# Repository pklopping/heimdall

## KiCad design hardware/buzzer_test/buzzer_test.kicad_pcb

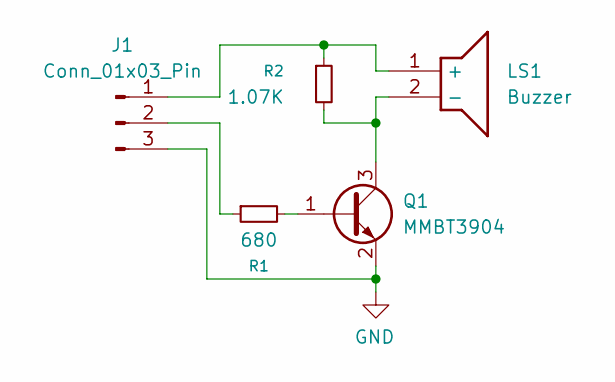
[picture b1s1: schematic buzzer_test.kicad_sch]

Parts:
J1: Conn_01x03_Pin; PinHeader_1x03_P2.54mm_Vertical
LS1: Buzzer; CMT1075SMTTR; Mouser Part Number 490-CMT-1075-SMT-TR
Q1: MMBT3904; SOT-23
R1: 680; R_0805_2012Metric
R2: 1.07K; R_0805_2012Metric

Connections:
GND: J1.3, Q1.2 (E)
unnamed: J1.1, LS1.1 (+), R2.1
unnamed: J1.2, R1.1
unnamed: LS1.2 (-), Q1.3 (C), R2.2
unnamed: Q1.1 (B), R1.2

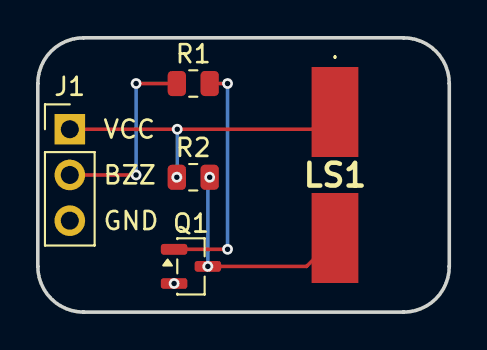
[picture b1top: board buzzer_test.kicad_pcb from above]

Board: 2 copper layers, 22.9 x 15.2 mm, 5 parts (0 on the bottom side), 5 nets.

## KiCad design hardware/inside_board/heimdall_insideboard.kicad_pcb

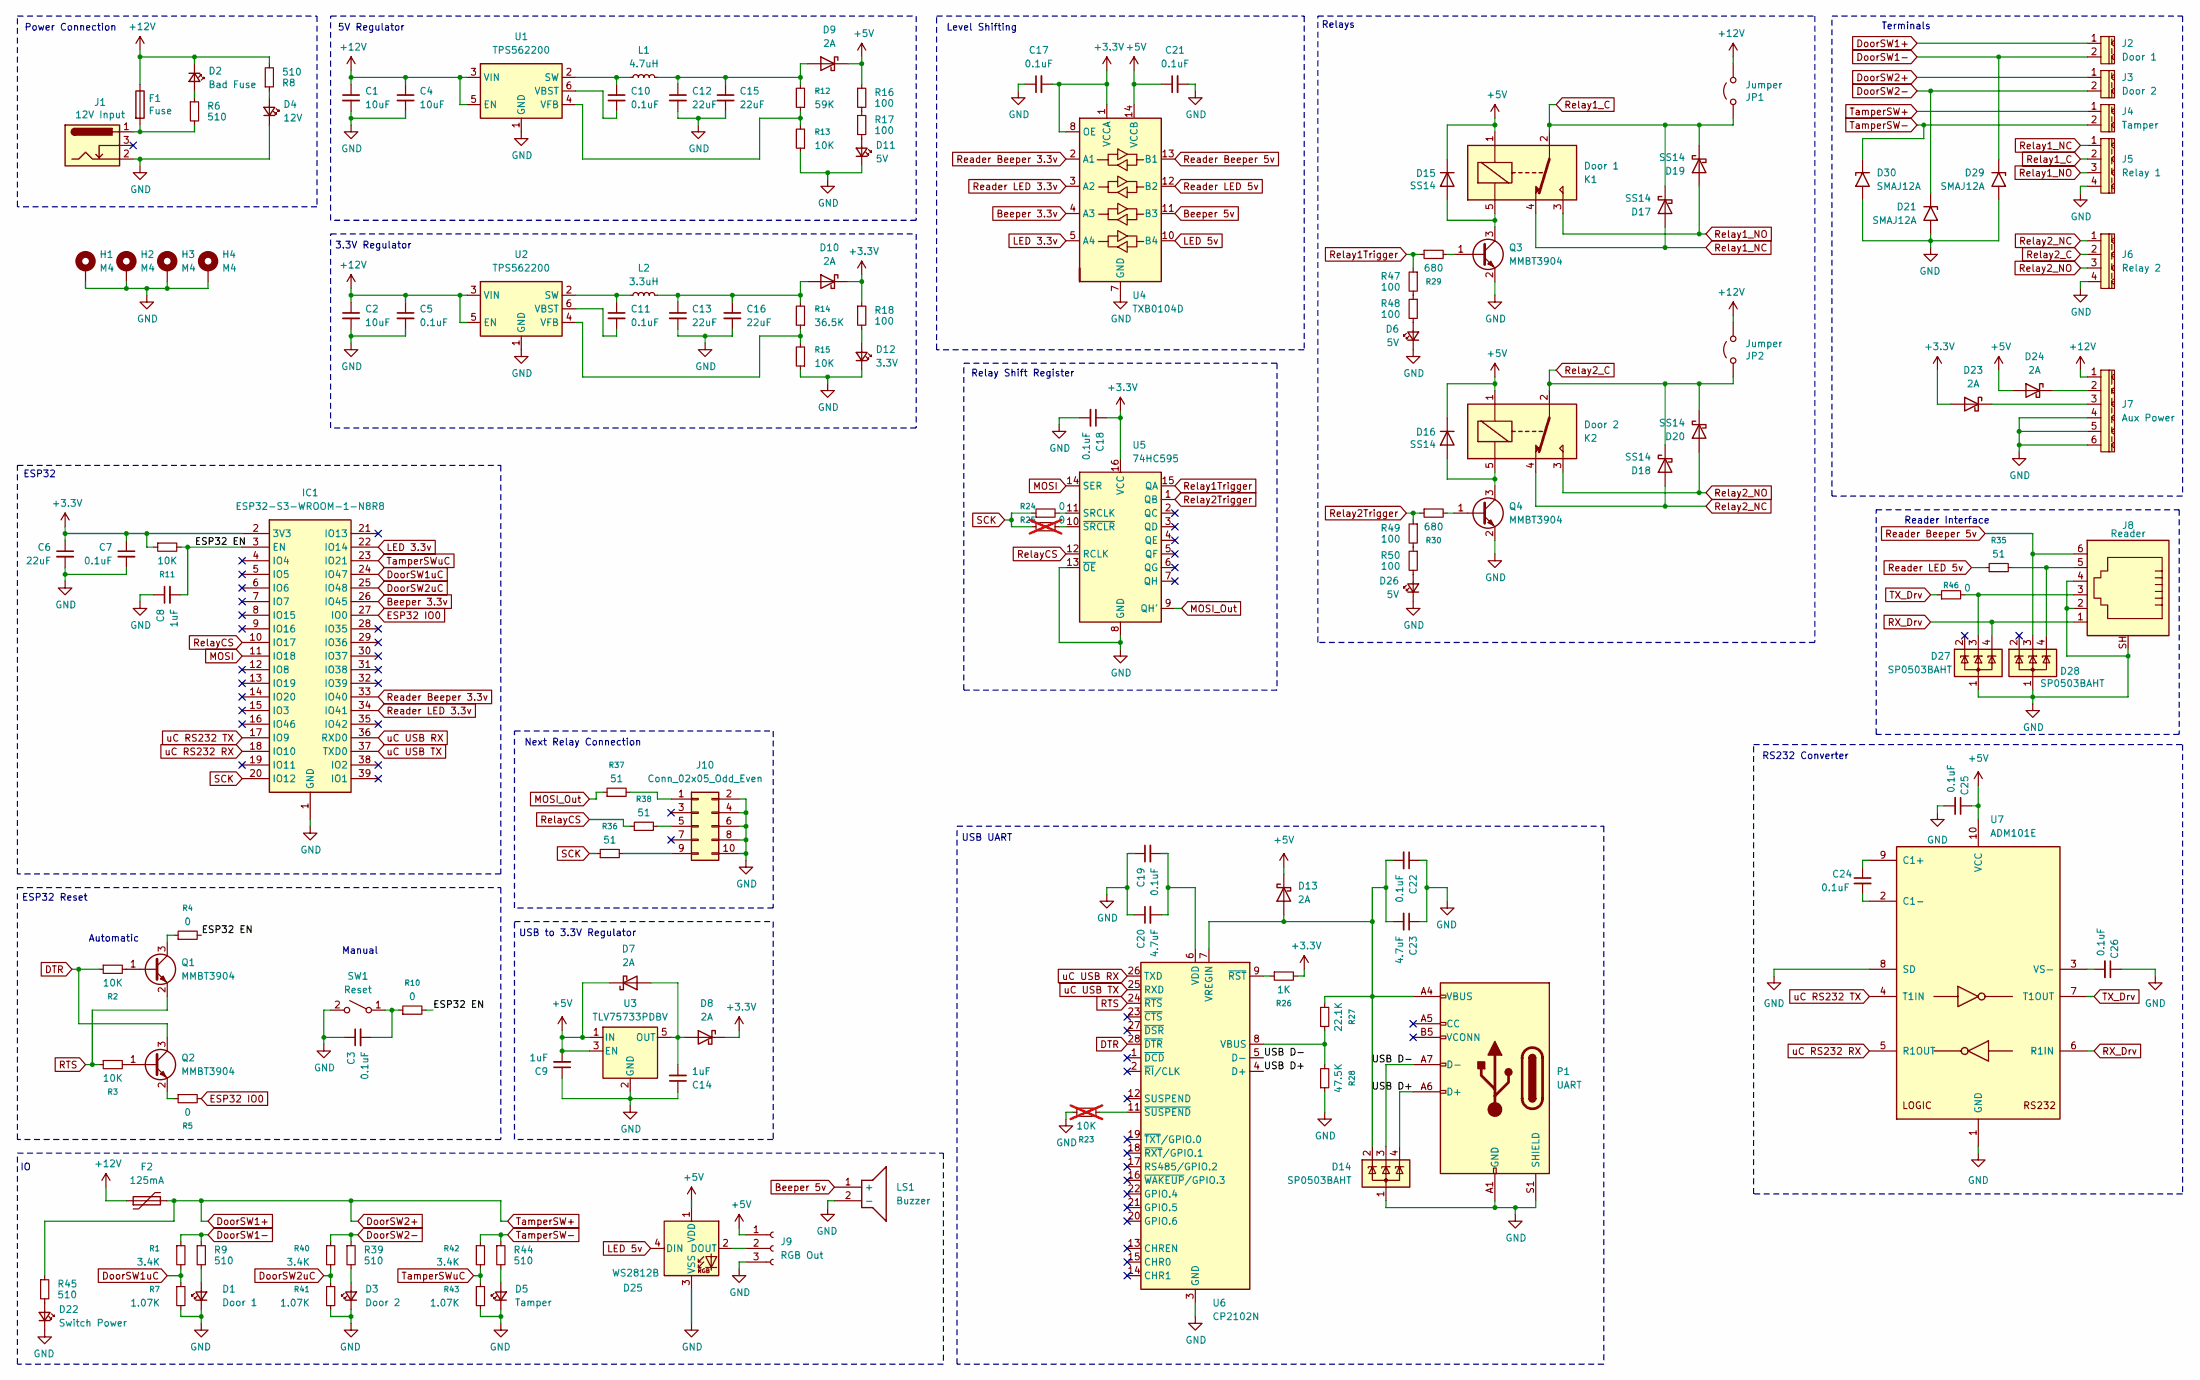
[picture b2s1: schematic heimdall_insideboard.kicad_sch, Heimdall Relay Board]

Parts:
C1, C2, C4: 10uF; C_0805_2012Metric
C3, C5, C7, C10, C11, C17, C18, C19, C21, C22, C24, C25, C26: 0.1uF; C_0805_2012Metric
C6, C12, C13, C15, C16: 22uF; C_0805_2012Metric
C8, C9, C14: 1uF; C_0805_2012Metric
C20, C23: 4.7uF; C_0805_2012Metric
D1: Door 1; LED_0805_2012Metric
D2: Bad Fuse; LED_0805_2012Metric
D3: Door 2; LED_0805_2012Metric
D4: 12V; LED_0805_2012Metric
D5: Tamper; LED_0805_2012Metric
D6, D11, D26: 5V; LED_0805_2012Metric
D7, D8, D9, D10, D13, D23, D24: 2A; D_SMB
D12: 3.3V; LED_0805_2012Metric
D14, D27, D28: SP0503BAHT; SOT-143
D15, D16, D17, D18, D19, D20: SS14; D_SMA
D21, D29, D30: SMAJ12A; D_SMA
D22: Switch Power; LED_0805_2012Metric
D25: WS2812B; LED_WS2812B_PLCC4_5.0x5.0mm_P3.2mm
F1: Fuse; Fuseholder_Clip-5x20mm_Littelfuse_521_Lateral_P17.00x5.00mm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
F2: 125mA; Fuse_1206_3216Metric
H1, H2, H3, H4: M4; MountingHole_4.3mm_M4_Pad_Via
IC1: ESP32-S3-WROOM-1-N8R8; ESP32S3WROOM1N8R8; Mouser Part Number 356-EP32S3WROOM1N8R8
J1: 12V Input; BarrelJack_Wuerth_6941xx301002
J2: Door 1; 1759017
J3: Door 2; 1759017
J4: Tamper; 1759017
J5: Relay 1; 1759033
J6: Relay 2; 1759033
J7: Aux Power; 1759059
J8: Reader; CRJ0241TH
J9: RGB Out; PinHeader_1x03_P2.54mm_Vertical
J10: Conn_02x05_Odd_Even; 75869-101LF
JP1, JP2: Jumper; PinHeader_1x03_P2.54mm_Vertical
K1: Door 1; G6RN17EASICFHADC5; Manufacturer_Part_Number G6RN-17-E-ASI-CF-HA DC5
K2: Door 2; G6RN17EASICFHADC5; Manufacturer_Part_Number G6RN-17-E-ASI-CF-HA DC5
L1: 4.7uH; SRR1260A4R7Y
L2: 3.3uH; SRR1260A4R7Y
LS1: Buzzer; CMT1075SMTTR; Mouser Part Number 490-CMT-1075-SMT-TR
P1: UART; USB4920-00-A
Q1, Q2, Q3, Q4: MMBT3904; SOT-23
R1, R40, R42: 3.4K; R_0805_2012Metric
R2, R3, R11, R13, R15: 10K; R_0805_2012Metric
R4, R5, R10, R24, R46: 0; R_0805_2012Metric
R6, R8, R9, R39, R44, R45: 510; R_0805_2012Metric
R7, R41, R43: 1.07K; R_0805_2012Metric
R12: 59K; R_0805_2012Metric
R14: 36.5K; R_0805_2012Metric
R16, R17, R18, R47, R48, R49, R50: 100; R_0805_2012Metric
R23: 10K; R_0805_2012Metric; not fitted
R25: 0; R_0805_2012Metric; not fitted
R26: 1K; R_0805_2012Metric
R27: 22.1K; R_0805_2012Metric
R28: 47.5K; R_0805_2012Metric
R29, R30: 680; R_0805_2012Metric
R35, R36, R37, R38: 51; R_0805_2012Metric
SW1: Reset; SW_SPST_Omron_B3FS-100xP
U1, U2: TPS562200; SOT-23-6
U3: TLV75733PDBV; SOT-23-5
U4: TXB0104D; SOIC-14_3.9x8.7mm_P1.27mm
U5: 74HC595; SOIC-16W_7.5x10.3mm_P1.27mm
U6: CP2102N; QFN-28-1EP_5x5mm_P0.5mm_EP3.35x3.35mm
U7: ADM101E; MSOP-10_3x3mm_P0.5mm

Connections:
+3.3V: C6.1, C7.1, C17.2, C18.1, D8.1 (K), D10.1 (K), D23.2 (A), IC1.2 (3V3), R11.1, R18.1, R26.2, U4.1 (VCCA), U4.8 (OE), U5.16 (VCC)
+5V: C9.2, C21.1, C25.1, D7.1 (K), D9.1 (K), D13.1 (K), D15.1 (K), D16.1 (K), D24.2 (A), D25.1 (VDD), J9.1, K1.1, K2.1, R16.1, U3.1 (IN), U3.3 (EN), U4.14 (VCCB), U7.10 (VCC)
+12V: C1.1, C2.1, C4.1, C5.1, D2.1 (K), F1.1, F2.1, J7.1, JP1.1 (A), JP2.1 (A), R8.2, U1.3 (VIN), U1.5 (EN), U2.3 (VIN), U2.5 (EN)
/ESP32 EN: C8.2, IC1.3 (EN), R4.2, R10.2, R11.2
/USB D+: D14.4 (K), P1.A6 (D+), U6.4 (D+)
/USB D-: D14.3 (K), P1.A7 (D-), U6.5 (D-)
Beeper 3.3v: IC1.26 (IO45), U4.4 (A3)
Beeper 5v: LS1.1 (+), U4.11 (B3)
DTR: Q2.3 (C), R2.1, U6.28 (~DTR)
DoorSW1+: F2.2, J2.1, J3.1, J4.1, R45.1
DoorSW1-: D29.1 (A1), J2.2, R1.1, R9.1
DoorSW1uC: IC1.24 (IO47), R1.2, R7.1
DoorSW2-: D21.1 (A1), J3.2, R39.1, R40.1
DoorSW2uC: IC1.25 (IO48), R40.2, R41.1
ESP32 IO0: IC1.27 (IO0), R5.2
GND: C1.2, C2.2, C3.1, C4.2, C5.2, C6.2, C7.2, C8.1, C9.1, C12.2, C13.2, C14.1, C15.2, C16.2, C17.1, C18.2, C19.1, C20.1, C21.2, C22.1, C23.1, C25.2, C26.1, D1.1 (K), D3.1 (K), D4.1 (K), D5.1 (K), D6.1 (K), D11.1 (K), D12.1 (K), D14.1 (A), D21.2 (A2), D22.1 (K), D25.3 (VSS), D26.1 (K), D27.1 (A), D28.1 (A), D29.2 (A2), D30.2 (A2), H1.1, H2.1, H3.1, H4.1, IC1.1 (GND), J1.2, J5.4, J6.4, J7.4, J7.5, J7.6, J8.2, J8.4, J8.SH, J9.3, J10.2, J10.4, J10.6, J10.8, J10.10, LS1.2 (-), P1.A1 (GND), P1.A12 (GND), P1.B1 (GND), P1.B12 (GND), P1.S1 (SHIELD), Q3.2 (E), Q4.2 (E), R7.2, R13.1, R15.1, R23.1, R28.1, R41.2, R43.2, SW1.2 (B), U1.1 (GND), U2.1 (GND), U3.2 (GND), U4.7 (GND), U5.8 (GND), U5.13 (~OE), U6.3 (GND), U6.29 (GND), U7.1 (GND), U7.8 (SD)
LED 3.3v: IC1.22 (IO14), U4.5 (A4)
LED 5v: D25.4 (DIN), U4.10 (B4)
MOSI: IC1.11 (IO18), U5.14 (SER)
MOSI_Out: R37.1, U5.9 (QH')
unnamed: D1.2 (A), R9.2
unnamed: D2.2 (A), R6.1
unnamed: D3.2 (A), R39.2
unnamed: D4.2 (A), R8.1
unnamed: D5.2 (A), R44.2
unnamed: D6.2 (A), R48.2
unnamed: C14.2, D7.2 (A), D8.2 (A), U3.5 (OUT)
unnamed: C12.1, C15.1, D9.2 (A), L1.2, R12.2
unnamed: C13.1, C16.1, D10.2 (A), L2.2, R14.2
unnamed: D11.2 (A), R17.2
unnamed: D12.2 (A), R18.2
unnamed: C22.2, C23.2, D13.2 (A), D14.2 (K), P1.A4 (VBUS), P1.A9 (VBUS), P1.B4 (VBUS), P1.B9 (VBUS), R27.2, U6.7 (VREGIN)
unnamed: D15.2 (A), K1.5, Q3.3 (C)
unnamed: D16.2 (A), K2.5, Q4.3 (C)
unnamed: D22.2 (A), R45.2
unnamed: D23.1 (K), J7.3
unnamed: D24.1 (K), J7.2
unnamed: D25.2 (DOUT), J9.2
unnamed: D26.2 (A), R50.2
unnamed: D27.3 (K), J8.3, R46.2
unnamed: D28.4 (K), J8.5, R35.2
unnamed: F1.2, J1.1, R6.2
unnamed: J10.1, R37.2
unnamed: J10.5, R38.2
unnamed: J10.9, R36.2
unnamed: Q1.1 (B), R2.2
unnamed: Q1.3 (C), R4.1
unnamed: Q2.1 (B), R3.2
unnamed: Q2.2 (E), R5.1
unnamed: Q3.1 (B), R29.2
unnamed: Q4.1 (B), R30.2
unnamed: R16.2, R17.1
unnamed: R47.2, R48.1
unnamed: R49.2, R50.1
unnamed: C3.2, R10.1, SW1.1 (A)
unnamed: C10.1, L1.1, U1.2 (SW)
unnamed: C10.2, U1.6 (VBST)
unnamed: R12.1, R13.2, U1.4 (VFB)
unnamed: C11.1, L2.1, U2.2 (SW)
unnamed: C11.2, U2.6 (VBST)
unnamed: R14.1, R15.2, U2.4 (VFB)
unnamed: R24.2, U5.11 (SRCLK)
unnamed: R25.2, U5.10 (~SRCLR)
unnamed: R27.1, R28.2, U6.8 (VBUS)
unnamed: C19.2, C20.2, U6.6 (VDD)
unnamed: R26.1, U6.9 (~RST)
unnamed: R23.2, U6.11 (~SUSPEND)
unnamed: C24.1, U7.9 (C1+)
unnamed: C24.2, U7.2 (C1-)
unnamed: C26.2, U7.3 (VS-)
RTS: Q1.2 (E), R3.1, U6.24 (~RTS)
RX_Drv: D27.4 (K), J8.1, U7.6 (R1IN)
Reader Beeper 3.3v: IC1.33 (IO40), U4.2 (A1)
Reader Beeper 5v: D28.3 (K), J8.6, U4.13 (B1)
Reader LED 3.3v: IC1.34 (IO41), U4.3 (A2)
Reader LED 5v: R35.1, U4.12 (B2)
Relay1Trigger: R29.1, R47.1, U5.15 (QA)
Relay1_C: D17.1 (K), D19.1 (K), J5.2, JP1.2 (B), K1.2
Relay1_NC: D17.2 (A), J5.1, K1.4
Relay1_NO: D19.2 (A), J5.3, K1.3
Relay2Trigger: R30.1, R49.1, U5.1 (QB)
Relay2_C: D18.1 (K), D20.1 (K), J6.2, JP2.2 (B), K2.2
Relay2_NC: D18.2 (A), J6.1, K2.4
Relay2_NO: D20.2 (A), J6.3, K2.3
RelayCS: IC1.10 (IO17), R38.1, U5.12 (RCLK)
SCK: IC1.20 (IO12), R24.1, R25.1, R36.1
TX_Drv: R46.1, U7.7 (T1OUT)
TamperSW-: D30.1 (A1), J4.2, R42.1, R44.1
TamperSWuC: IC1.23 (IO21), R42.2, R43.1
uC RS232 RX: IC1.18 (IO10), U7.5 (R1OUT)
uC RS232 TX: IC1.17 (IO9), U7.4 (T1IN)
uC USB RX: IC1.36 (RXD0), U6.26 (TXD)
uC USB TX: IC1.37 (TXD0), U6.25 (RXD)

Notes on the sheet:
Power Connection
Relay Shift Register
Automatic
RS232 Converter
ESP32 Reset
USB to 3.3V Regulator
Terminals
Next Relay Connection
Manual
3.3V Regulator
5V Regulator
Reader Interface
Relays
Level Shifting
USB UART
ESP32

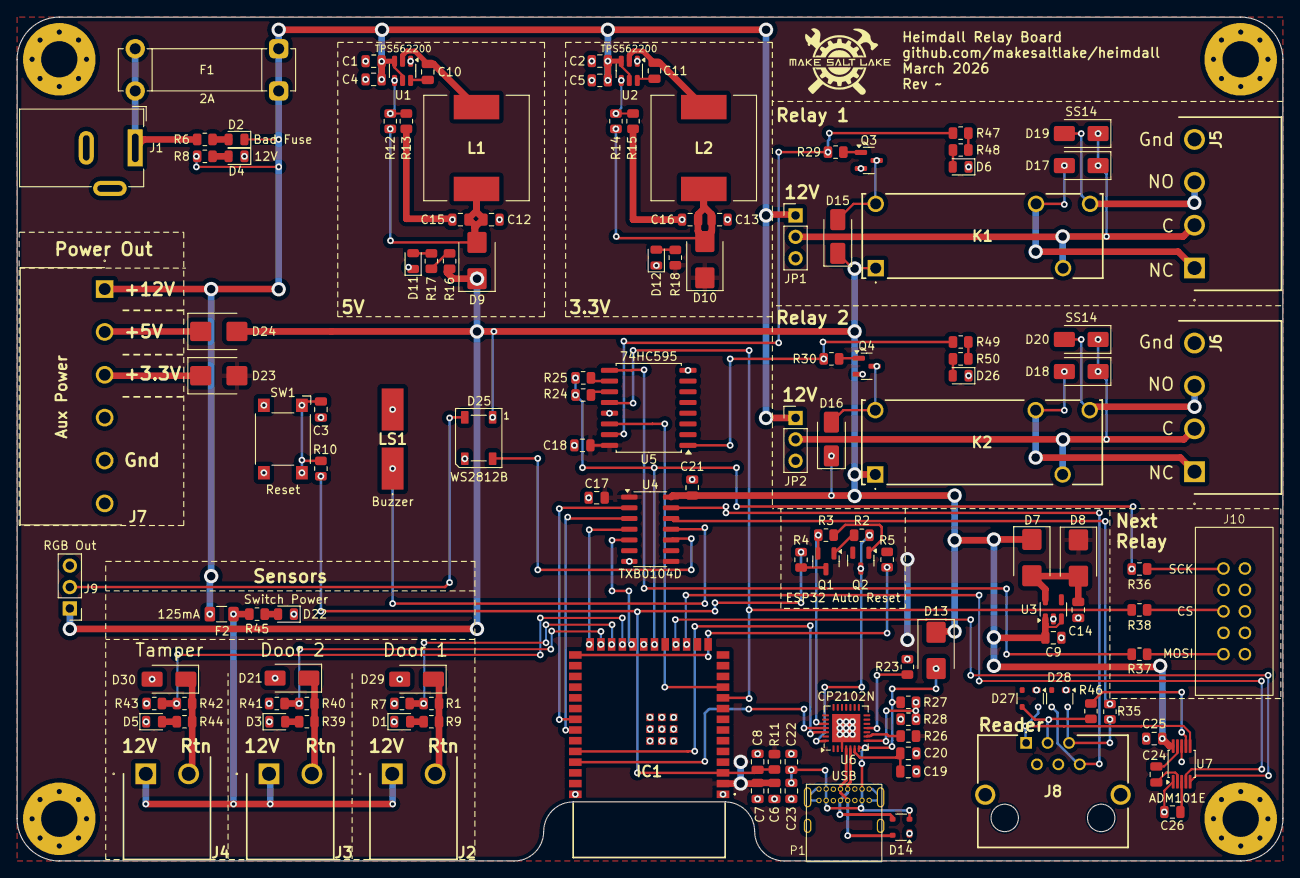
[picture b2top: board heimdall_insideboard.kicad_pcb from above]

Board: 2 copper layers, 150.0 x 100.0 mm, 135 parts (0 on the bottom side), 93 nets.

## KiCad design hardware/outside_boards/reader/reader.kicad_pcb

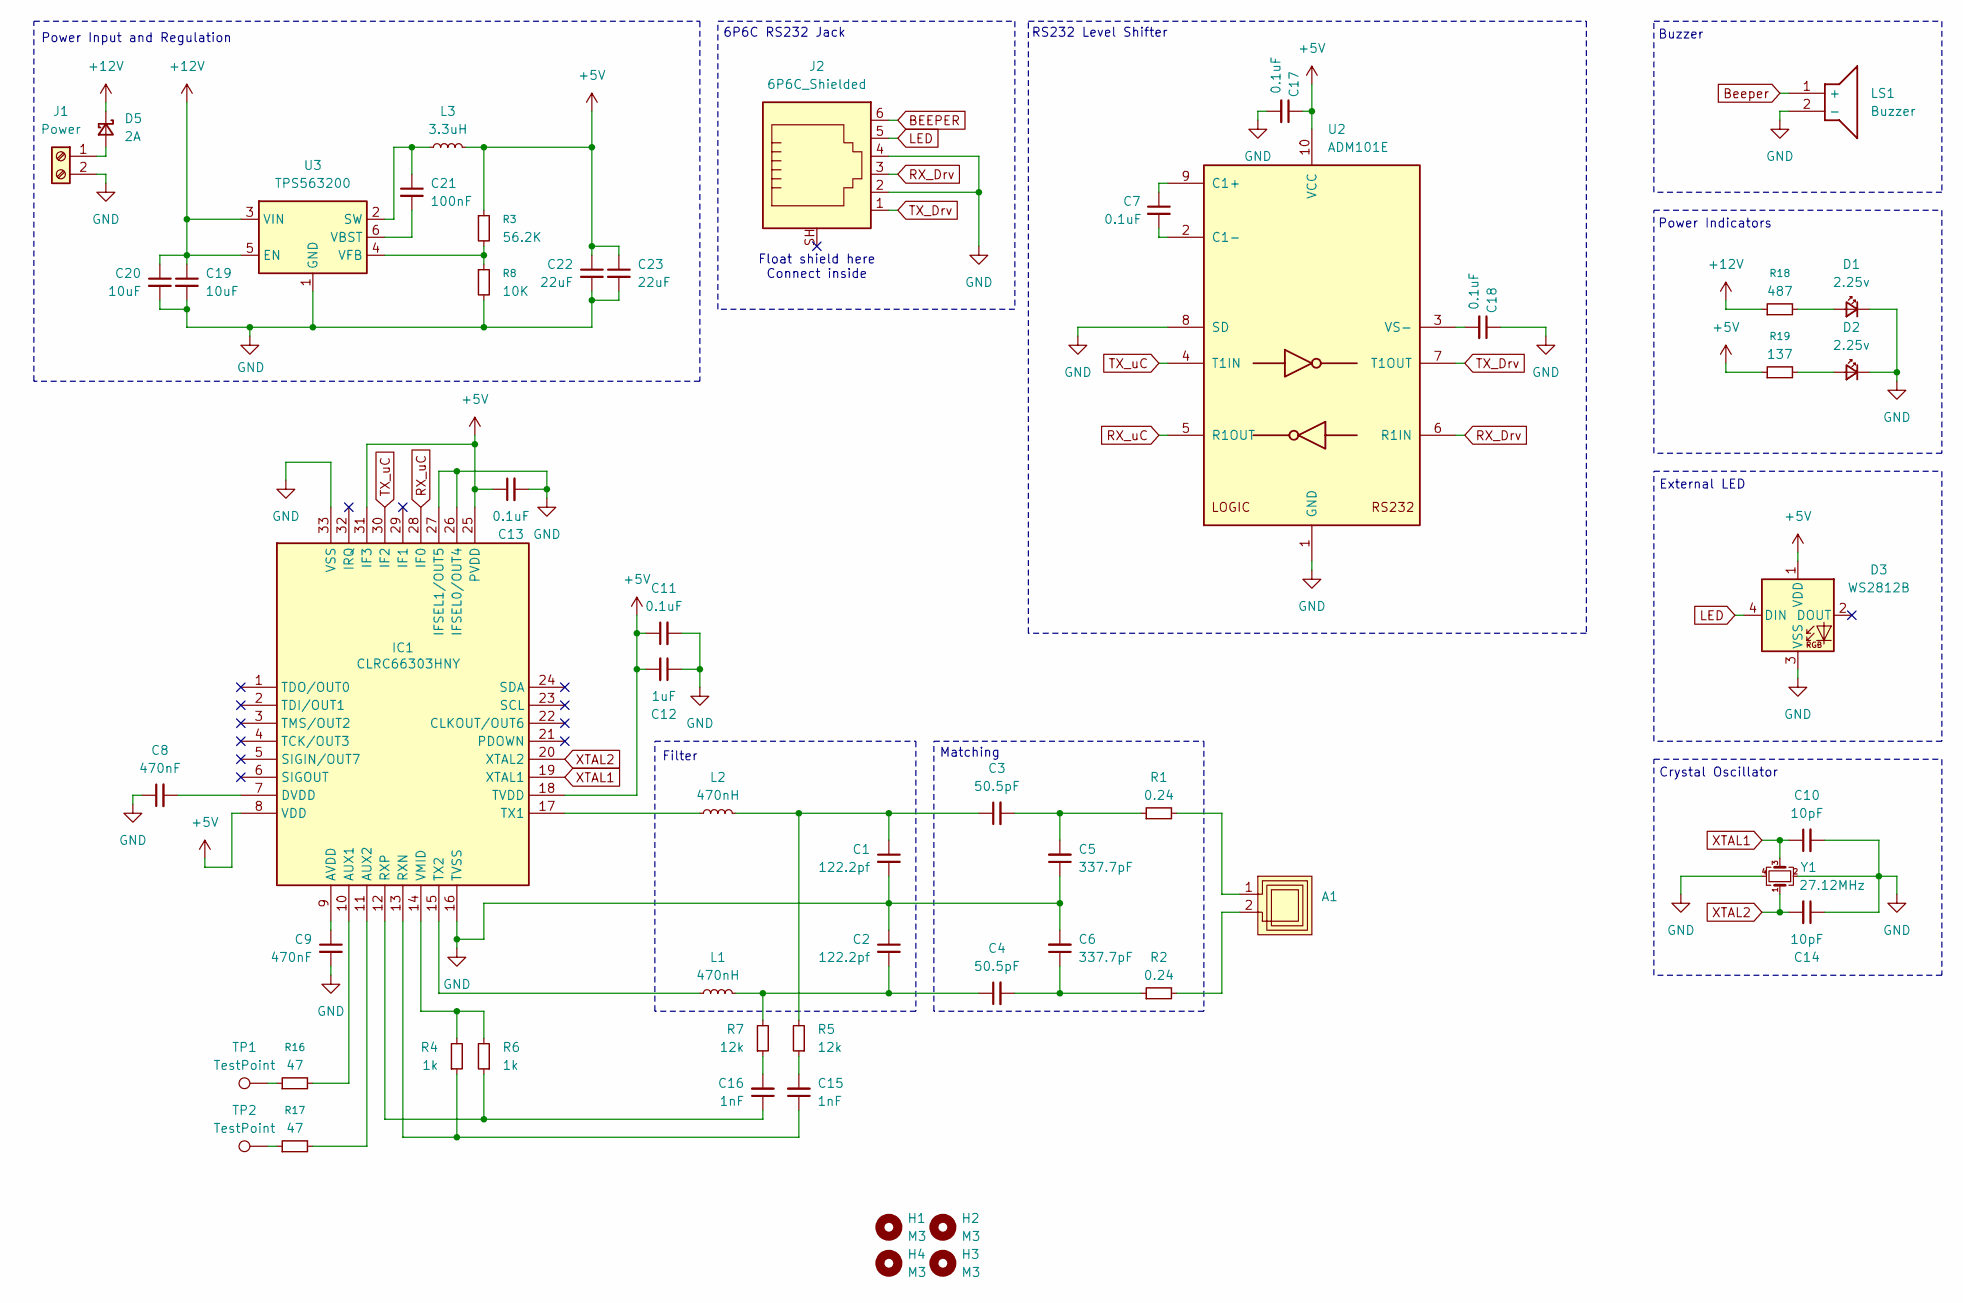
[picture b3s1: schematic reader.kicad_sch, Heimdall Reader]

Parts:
A1: Anetnna_50x50
C1, C2: 122.2pf; C_0805_2012Metric
C3, C4: 50.5pF; C_0805_2012Metric
C5, C6: 337.7pF; C_0805_2012Metric
C7, C11, C13, C17, C18: 0.1uF; C_0805_2012Metric
C8, C9: 470nF; C_0805_2012Metric
C10, C14: 10pF; C_0805_2012Metric
C12: 1uF; C_0805_2012Metric
C15, C16: 1nF; C_0805_2012Metric
C19, C20: 10uF; C_0805_2012Metric
C21: 100nF; C_0805_2012Metric
C22, C23: 22uF; C_0805_2012Metric
D1, D2: 2.25v; LED_0805_2012Metric
D3: WS2812B; LED_WS2812B_PLCC4_5.0x5.0mm_P3.2mm
D5: 2A; D_1206_3216Metric
H1, H2, H3, H4: M3; MountingHole_3.2mm_M3
IC1: CLRC66303HNY; QFN50P500X500X100-33N; Mouser Part Number 771-CLRC66303HNY
J1: Power; 1991095
J2: 6P6C_Shielded; CRJ0241TH
L1, L2: 470nH; L_0805_2012Metric
L3: 3.3uH; L_TDK_VLS6045EX_VLS6045AF
LS1: Buzzer; CMT1075SMTTR; Mouser Part Number 490-CMT-1075-SMT-TR
R1, R2: 0.24; R_0805_2012Metric
R3: 56.2K; R_0805_2012Metric
R4, R6: 1k; R_0805_2012Metric
R5, R7: 12k; R_0805_2012Metric
R8: 10K; R_0805_2012Metric
R16, R17: 47; R_0805_2012Metric
R18: 487; R_0805_2012Metric
R19: 137; R_0805_2012Metric
TP1, TP2: TestPoint; TestPoint_Pad_D1.5mm
U2: ADM101E; MSOP-10_3x3mm_P0.5mm
U3: TPS563200; SOT-23-6
Y1: 27.12MHz; Crystal_SMD_3225-4Pin_3.2x2.5mm

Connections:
+5V: C11.1, C12.2, C13.1, C17.1, C22.1, C23.1, D3.1 (VDD), IC1.8 (VDD), IC1.18 (TVDD), IC1.25 (PVDD), IC1.31 (IF3), L3.2, R3.1, R19.1, U2.10 (VCC)
+12V: C19.1, C20.1, D5.1 (K), R18.1, U3.3 (VIN), U3.5 (EN)
BEEPER: J2.6
Beeper: LS1.1 (+)
GND: C1.2, C2.1, C5.1, C6.2, C8.1, C9.2, C10.2, C11.2, C12.1, C13.2, C14.1, C17.2, C18.1, C19.2, C20.2, C22.2, C23.2, D1.1 (K), D2.1 (K), D3.3 (VSS), IC1.16 (TVSS), IC1.26 (IFSEL0/OUT4), IC1.27 (IFSEL1/OUT5), IC1.33 (VSS), J1.2, J2.2, J2.4, LS1.2 (-), R8.2, U2.1 (GND), U2.8 (SD), U3.1 (GND), Y1.2, Y1.4
LED: D3.4 (DIN), J2.5
unnamed: A1.1, R1.2
unnamed: A1.2, R2.2
unnamed: C1.1, C3.1, L2.2, R5.2
unnamed: C2.2, C4.1, L1.2, R7.2
unnamed: C3.2, C5.2, R1.1
unnamed: C4.2, C6.1, R2.1
unnamed: C15.2, R5.1
unnamed: C16.2, R7.1
unnamed: D1.2 (A), R18.2
unnamed: D2.2 (A), R19.2
unnamed: D5.2 (A), J1.1
unnamed: IC1.10 (AUX1), R16.2
unnamed: IC1.11 (AUX2), R17.2
unnamed: C9.1, IC1.9 (AVDD)
unnamed: C8.2, IC1.7 (DVDD)
unnamed: C15.1, IC1.13 (RXN), R4.1
unnamed: C16.1, IC1.12 (RXP), R6.1
unnamed: IC1.17 (TX1), L2.1
unnamed: IC1.15 (TX2), L1.1
unnamed: IC1.14 (VMID), R4.2, R6.2
unnamed: R16.1, TP1.1
unnamed: R17.1, TP2.1
unnamed: C7.1, U2.9 (C1+)
unnamed: C7.2, U2.2 (C1-)
unnamed: C18.2, U2.3 (VS-)
unnamed: C21.1, L3.1, U3.2 (SW)
unnamed: C21.2, U3.6 (VBST)
unnamed: R3.2, R8.1, U3.4 (VFB)
RX_Drv: J2.3, U2.6 (R1IN)
RX_uC: IC1.28 (IF0), U2.5 (R1OUT)
TX_Drv: J2.1, U2.7 (T1OUT)
TX_uC: IC1.30 (IF2), U2.4 (T1IN)
XTAL1: C10.1, IC1.19 (XTAL1), Y1.3
XTAL2: C14.2, IC1.20 (XTAL2), Y1.1

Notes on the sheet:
External LED
Crystal Oscillator
Power Indicators
Matching
Float shield here Connect inside
Buzzer
6P6C RS232 Jack
Power Input and Regulation
RS232 Level Shifter
Filter

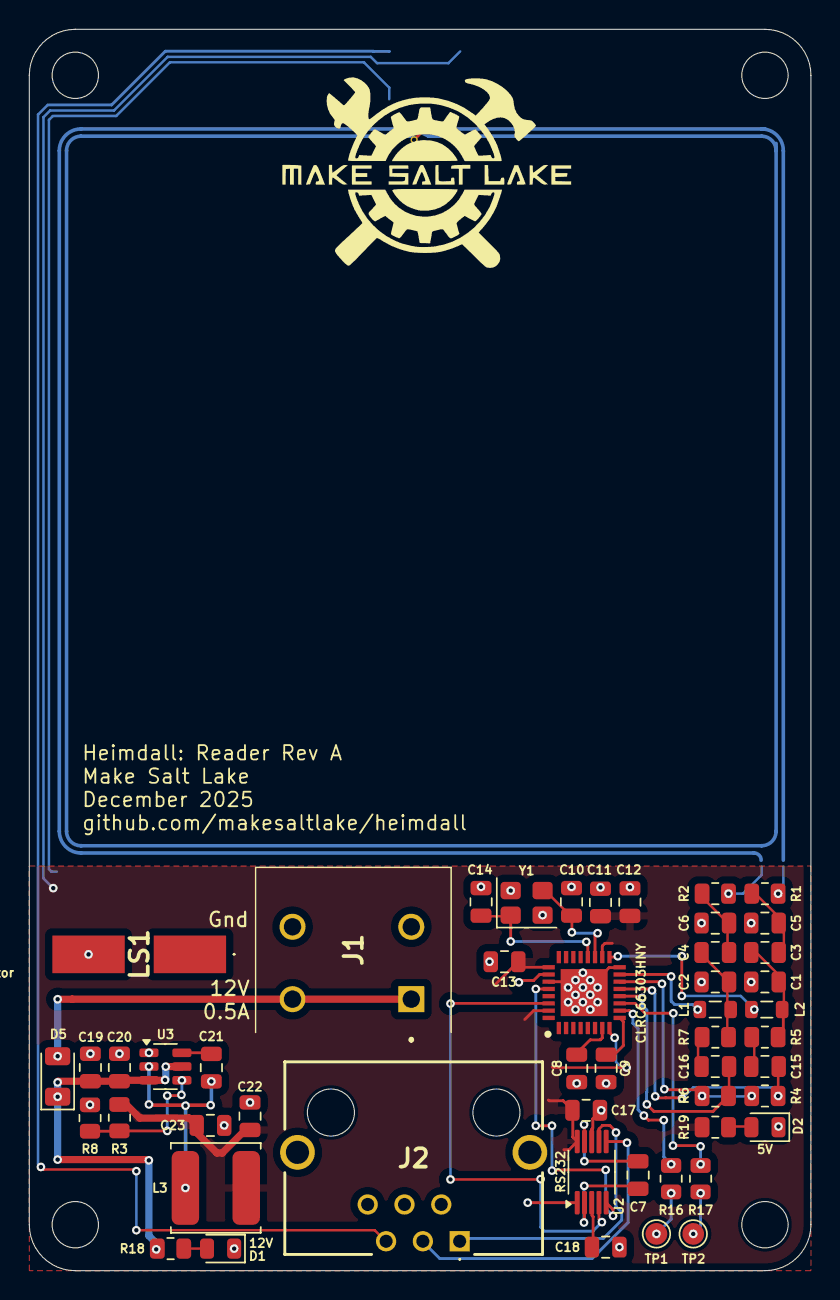
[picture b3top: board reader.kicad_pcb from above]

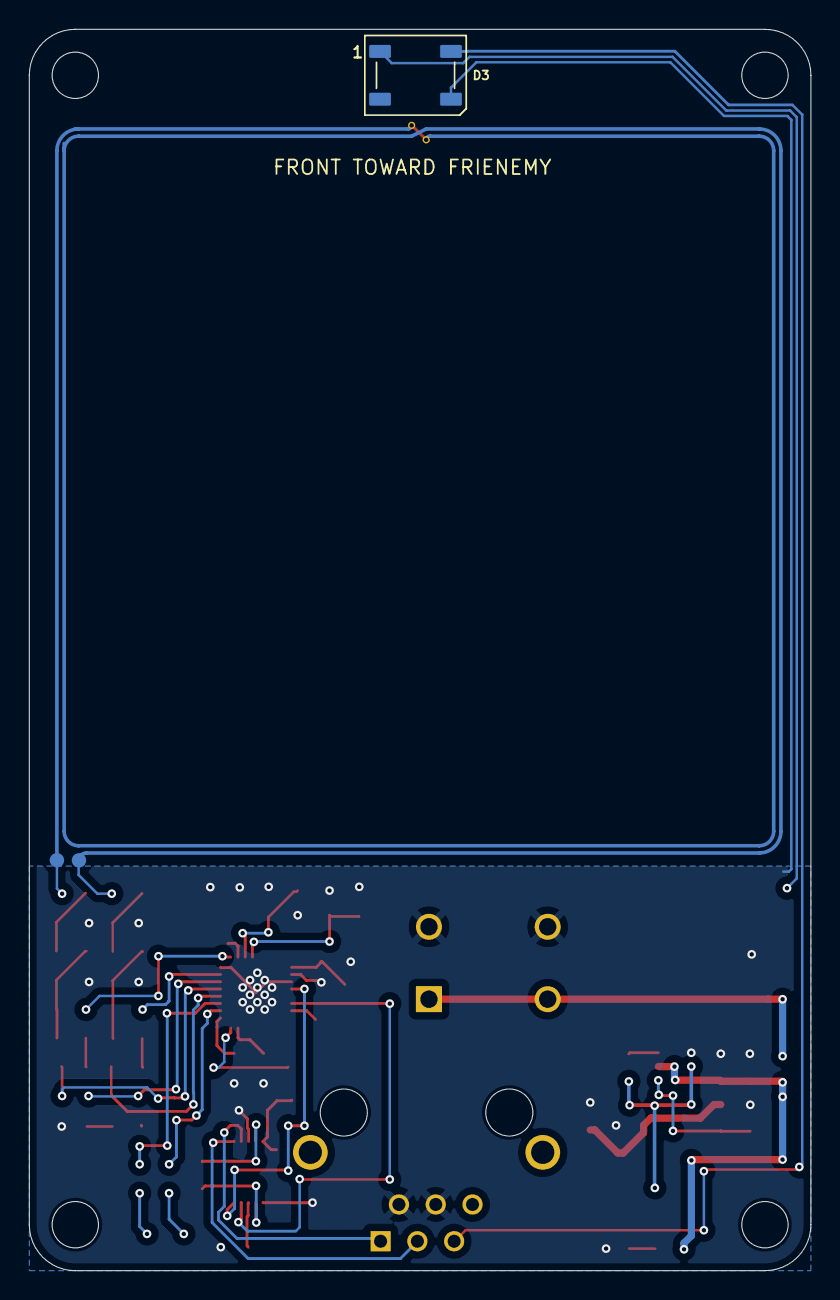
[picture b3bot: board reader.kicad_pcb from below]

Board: 2 copper layers, 54.0 x 85.7 mm, 56 parts (2 on the bottom side), 38 nets.

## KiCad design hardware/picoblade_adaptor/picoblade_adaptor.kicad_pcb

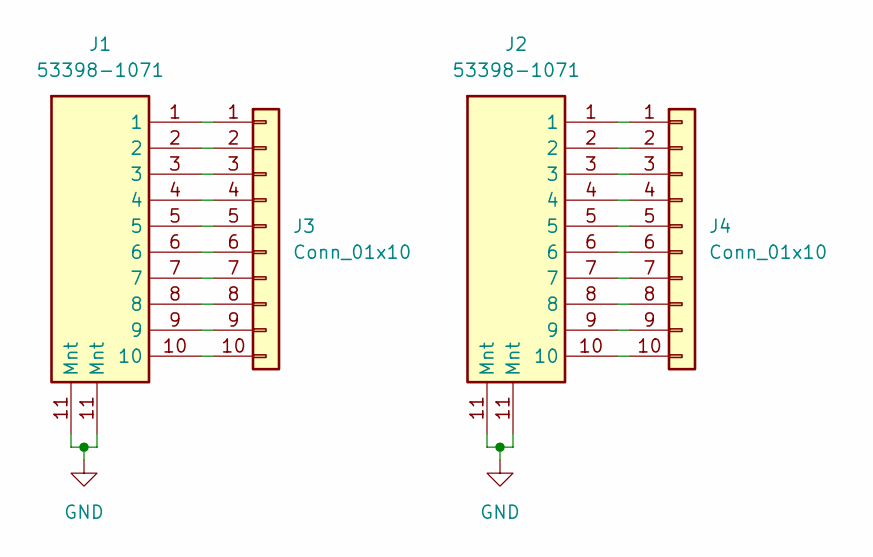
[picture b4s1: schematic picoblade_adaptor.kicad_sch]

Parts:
J1, J2: 53398-1071; 533981071; Mouser Part Number 538-53398-1071
J3, J4: Conn_01x10; PinHeader_1x10_P2.54mm_Vertical

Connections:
GND: J1.11 (Mnt), J2.11 (Mnt)
unnamed: J1.1, J3.1
unnamed: J1.2, J3.2
unnamed: J1.3, J3.3
unnamed: J1.4, J3.4
unnamed: J1.5, J3.5
unnamed: J1.6, J3.6
unnamed: J1.7, J3.7
unnamed: J1.8, J3.8
unnamed: J1.9, J3.9
unnamed: J1.10, J3.10
unnamed: J2.1, J4.1
unnamed: J2.2, J4.2
unnamed: J2.3, J4.3
unnamed: J2.4, J4.4
unnamed: J2.5, J4.5
unnamed: J2.6, J4.6
unnamed: J2.7, J4.7
unnamed: J2.8, J4.8
unnamed: J2.9, J4.9
unnamed: J2.10, J4.10

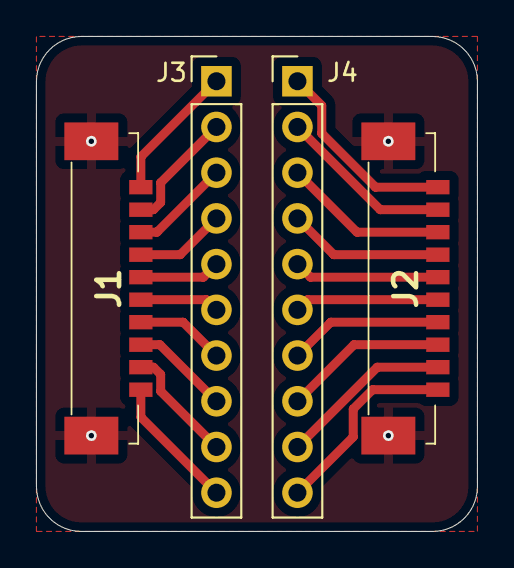
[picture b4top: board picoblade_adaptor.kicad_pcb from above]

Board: 2 copper layers, 24.5 x 27.5 mm, 4 parts (0 on the bottom side), 21 nets.

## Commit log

2025-09-20 Created RFID board, performed KiCAD organization/cleanup
2025-09-20 Fixing ESP32 symbol and footprint
2025-09-24 Updating schematic with datasheets and labels
2025-10-09 Inside board updates
2025-10-09 Cleaning up schematic
2025-10-09 Layout and page setup
2025-10-10 Adding LEDs
2025-10-10 Library cleanup, inside board progress
2025-10-17 Pico-blade adaptor pcb test
2025-10-17 Adding silkscreen to the adaptor
2025-11-06 Library updates
2025-12-01 Halfway through the conversion, prolly
2025-12-01 More layout and datasheets
2025-12-03 Playing with the layout and fixing footprints
2025-12-03 This layout is insane
2025-12-04 Layout
2025-12-04 PCB layout
2026-01-07 Updated schematic for switching powwer regulator
2026-01-07 Thinking about PCB layout
2026-01-07 Trying to fit everything
2026-01-20 Finished switching regulator layout
2026-04-02 Fixing datasheet link
2026-04-09 Transistor fixes
2026-04-12 Shift register OE
2026-04-12 SCK fix
2026-04-12 12V TVS, kinda
2026-04-14 TVS Diodes placed
2026-04-14 Buzzer pin update
2026-04-14 Deleted some jumpers post validation
2026-04-14 Cleaning up jumper resistors
2026-04-15 New buzzer who dis
2026-04-16 LED swap
2026-04-17 Buzzer test PCB
